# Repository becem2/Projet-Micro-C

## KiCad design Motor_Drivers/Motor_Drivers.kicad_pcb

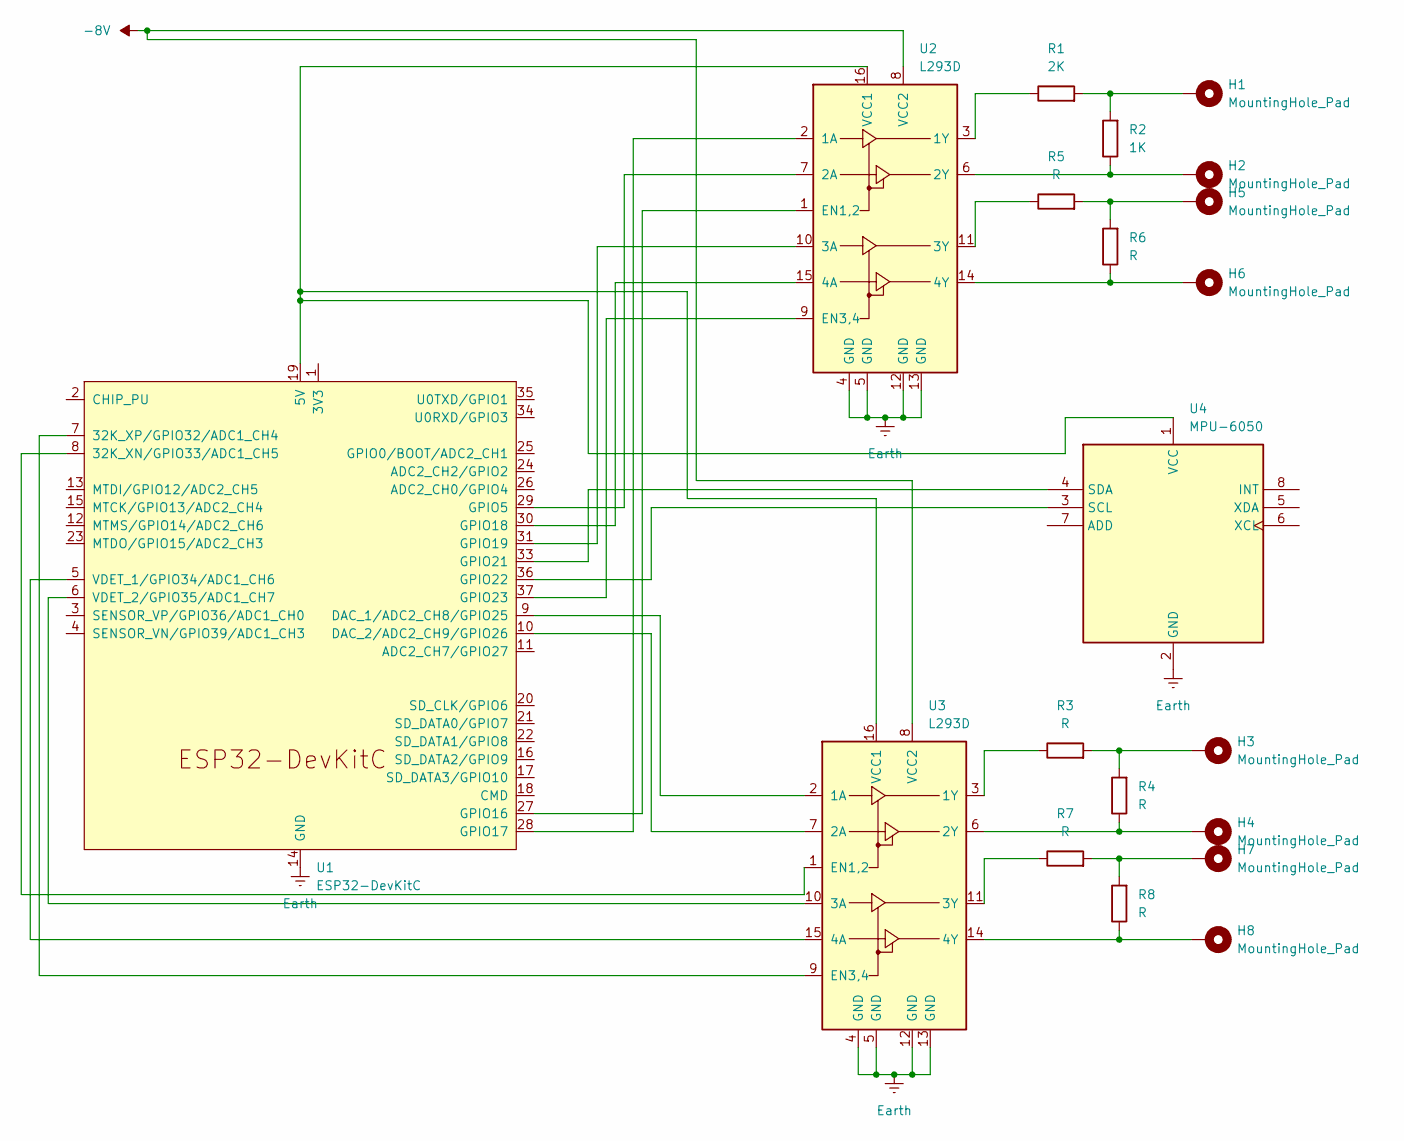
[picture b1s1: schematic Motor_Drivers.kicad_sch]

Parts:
H1, H2, H3, H4, H5, H6, H7, H8: MountingHole_Pad; TestPoint_Loop_D1.80mm_Drill1.0mm_Beaded
R1: 2K; R_Axial_DIN0204_L3.6mm_D1.6mm_P5.08mm_Horizontal
R2: 1K; R_Axial_DIN0204_L3.6mm_D1.6mm_P5.08mm_Horizontal
R3, R4, R5, R6, R7, R8: R; R_Axial_DIN0204_L3.6mm_D1.6mm_P5.08mm_Horizontal
U1: ESP32-DevKitC; ESP32_38pin
U2, U3: L293D; DIP-16_W7.62mm
U4: MPU-6050; module_mpu6050

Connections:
-8V: U2.8 (VCC2), U3.8 (VCC2)
Earth: U1.14 (GND), U1.32 (GND), U1.38 (GND), U2.4 (GND), U2.5 (GND), U2.12 (GND), U2.13 (GND), U3.4 (GND), U3.5 (GND), U3.12 (GND), U3.13 (GND), U4.2 (GND)
unnamed: H1.1, R1.2, R2.2
unnamed: H3.1, R3.2, R4.2
unnamed: H5.1, R5.2, R6.2
unnamed: H7.1, R7.2, R8.2
unnamed: U1.19 (5V), U2.16 (VCC1), U3.16 (VCC1), U4.1 (VCC)
unnamed: U1.8 (32K_XN/GPIO33/ADC1_CH5), U3.1 (EN1,2)
unnamed: U1.7 (32K_XP/GPIO32/ADC1_CH4), U3.9 (EN3,4)
unnamed: U1.9 (DAC_1/ADC2_CH8/GPIO25), U3.2 (1A)
unnamed: U1.10 (DAC_2/ADC2_CH9/GPIO26), U3.7 (2A)
unnamed: U1.29 (GPIO5), U2.7 (2A)
unnamed: U1.27 (GPIO16), U2.1 (EN1,2)
unnamed: U1.28 (GPIO17), U2.2 (1A)
unnamed: U1.30 (GPIO18), U2.15 (4A)
unnamed: U1.31 (GPIO19), U2.10 (3A)
unnamed: U1.33 (GPIO21), U4.4 (SDA)
unnamed: U1.36 (GPIO22), U4.3 (SCL)
unnamed: U1.37 (GPIO23), U2.9 (EN3,4)
unnamed: U1.5 (VDET_1/GPIO34/ADC1_CH6), U3.15 (4A)
unnamed: U1.6 (VDET_2/GPIO35/ADC1_CH7), U3.10 (3A)
unnamed: R1.1, U2.3 (1Y)
unnamed: H2.1, R2.1, U2.6 (2Y)
unnamed: R5.1, U2.11 (3Y)
unnamed: H6.1, R6.1, U2.14 (4Y)
unnamed: R3.1, U3.3 (1Y)
unnamed: H4.1, R4.1, U3.6 (2Y)
unnamed: R7.1, U3.11 (3Y)
unnamed: H8.1, R8.1, U3.14 (4Y)

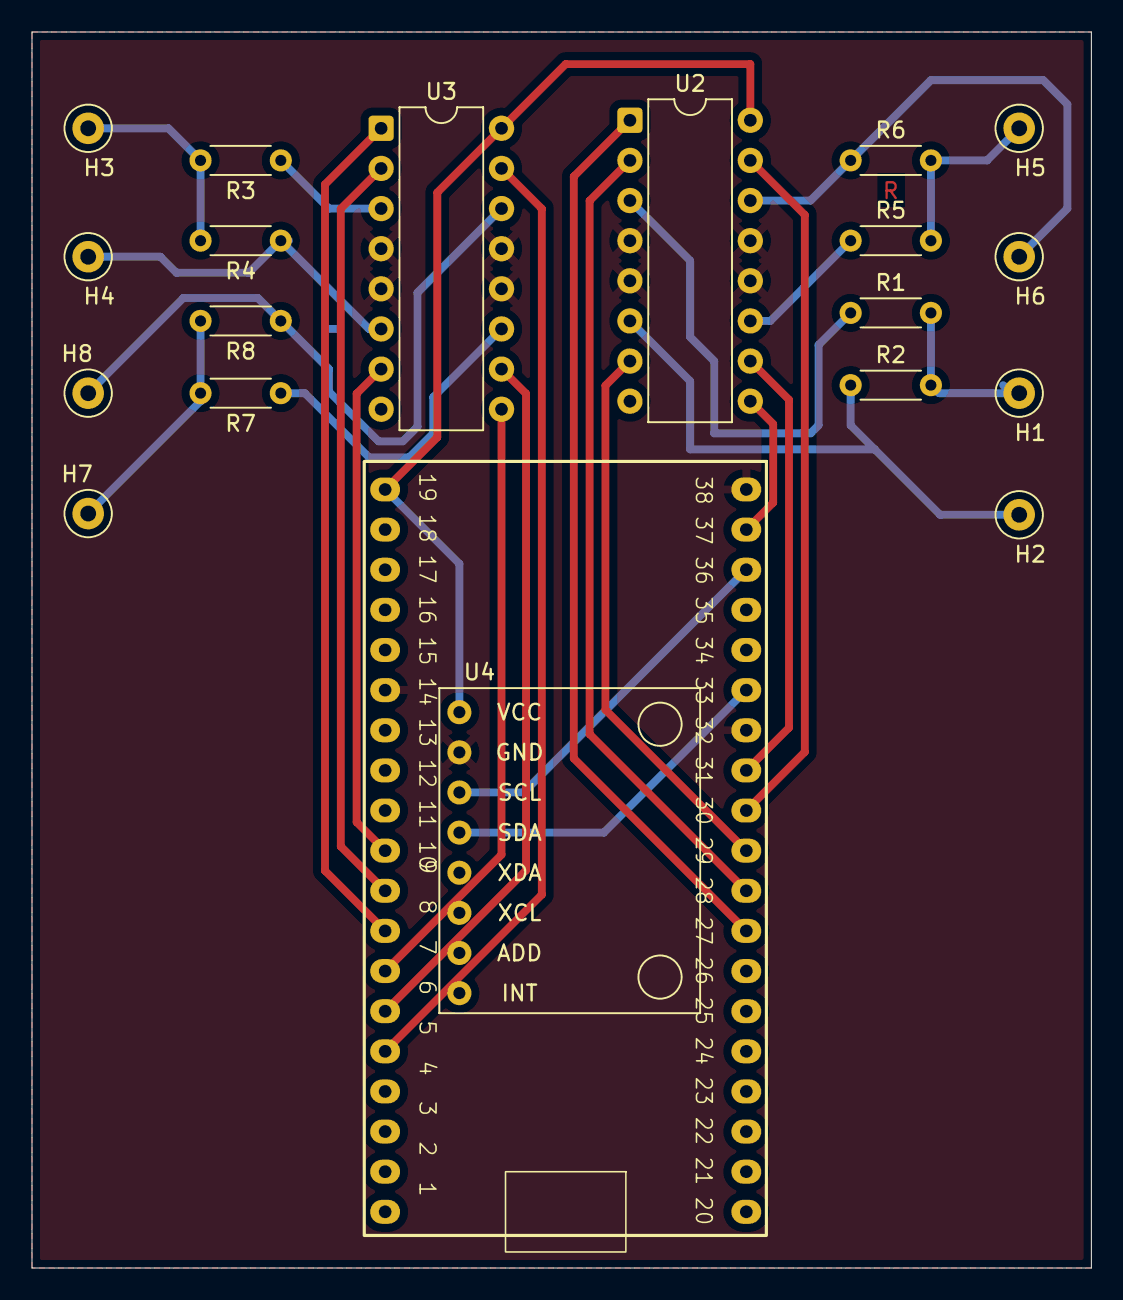
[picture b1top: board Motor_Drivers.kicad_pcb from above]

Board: 2 copper layers, 67.1 x 78.2 mm, 20 parts (0 on the bottom side), 29 nets.

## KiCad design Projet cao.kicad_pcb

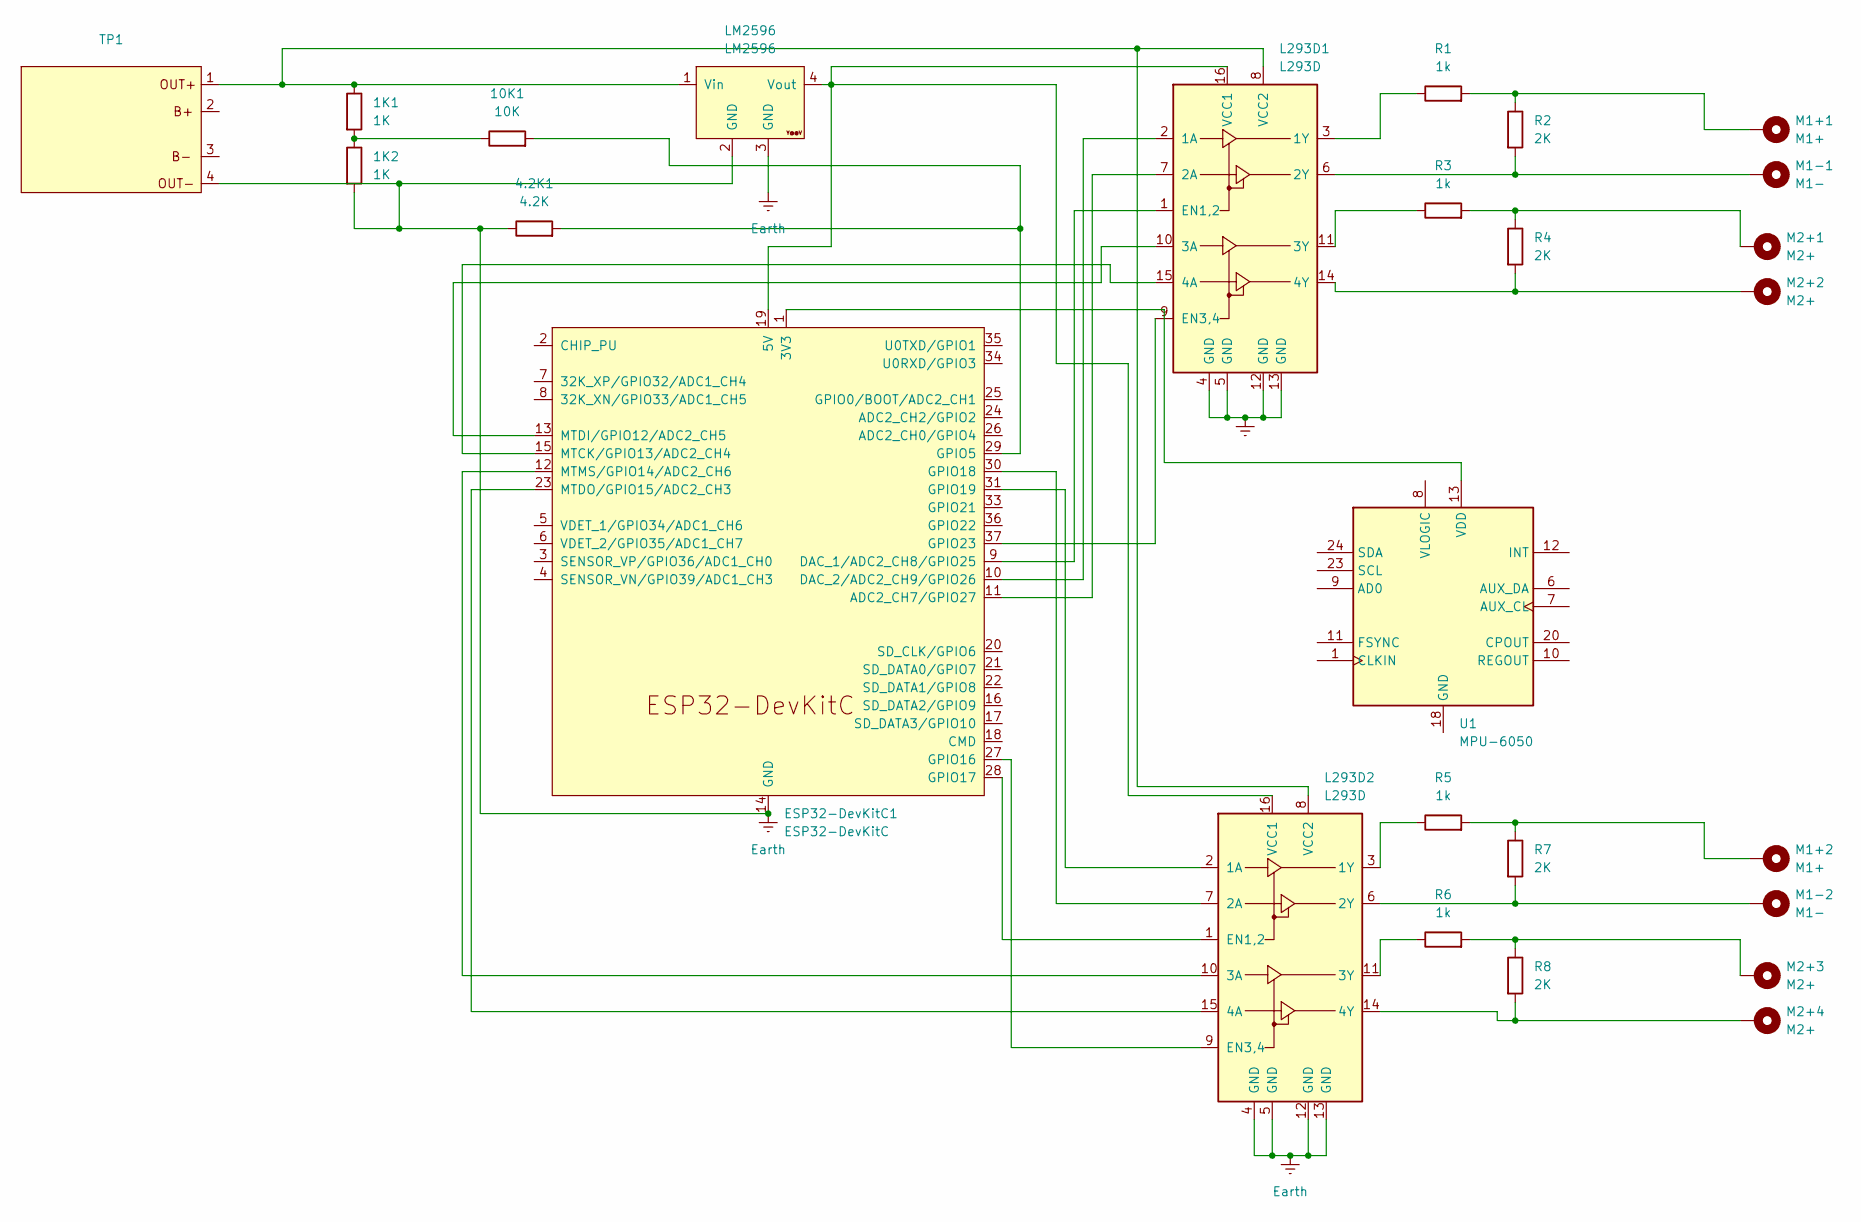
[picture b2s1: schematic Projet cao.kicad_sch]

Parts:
1K1, 1K2: 1K; R_Axial_DIN0204_L3.6mm_D1.6mm_P5.08mm_Horizontal
4.2K1: 4.2K; R_Axial_DIN0204_L3.6mm_D1.6mm_P5.08mm_Horizontal
10K1: 10K; R_Axial_DIN0204_L3.6mm_D1.6mm_P5.08mm_Horizontal
ESP32-DevKitC1: ESP32-DevKitC; ESP32_38pin
L293D1, L293D2: L293D; DIP-16_W7.62mm
LM2596: LM2596; YAAJ_DCDC_StepDown_LM2596
M1+1, M1+2: M1+; MountingHole_2.2mm_M2_ISO7380_Pad
M1-1, M1-2: M1-; MountingHole_2.2mm_M2_ISO7380_Pad
M2+1, M2+2, M2+3, M2+4: M2+; MountingHole_2.2mm_M2_ISO7380_Pad
R1, R3, R5, R6: 1k; R_Axial_DIN0204_L3.6mm_D1.6mm_P5.08mm_Horizontal
R2, R4, R7, R8: 2K; R_Axial_DIN0204_L3.6mm_D1.6mm_P5.08mm_Horizontal
TP1: TP4056-18650
U1: MPU-6050; module_mpu6050

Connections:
Earth: 1K2.2, 4.2K1.1, ESP32-DevKitC1.14 (GND), ESP32-DevKitC1.32 (GND), ESP32-DevKitC1.38 (GND), L293D1.4 (GND), L293D1.5 (GND), L293D1.12 (GND), L293D1.13 (GND), L293D2.4 (GND), L293D2.5 (GND), L293D2.12 (GND), L293D2.13 (GND), LM2596.2 (GND), LM2596.3 (GND), TP1.4
unnamed: 1K1.2, 1K2.1, 10K1.1
unnamed: ESP32-DevKitC1.1 (3V3), U1.13 (VDD)
unnamed: ESP32-DevKitC1.19 (5V), L293D1.16 (VCC1), L293D2.16 (VCC1), LM2596.4 (Vout)
unnamed: ESP32-DevKitC1.11 (ADC2_CH7/GPIO27), L293D1.7 (2A)
unnamed: ESP32-DevKitC1.9 (DAC_1/ADC2_CH8/GPIO25), L293D1.1 (EN1,2)
unnamed: ESP32-DevKitC1.10 (DAC_2/ADC2_CH9/GPIO26), L293D1.2 (1A)
unnamed: 4.2K1.2, 10K1.2, ESP32-DevKitC1.29 (GPIO5)
unnamed: ESP32-DevKitC1.27 (GPIO16), L293D2.9 (EN3,4)
unnamed: ESP32-DevKitC1.28 (GPIO17), L293D2.1 (EN1,2)
unnamed: ESP32-DevKitC1.30 (GPIO18), L293D2.7 (2A)
unnamed: ESP32-DevKitC1.31 (GPIO19), L293D2.2 (1A)
unnamed: ESP32-DevKitC1.37 (GPIO23), L293D1.9 (EN3,4)
unnamed: ESP32-DevKitC1.15 (MTCK/GPIO13/ADC2_CH4), L293D1.15 (4A)
unnamed: ESP32-DevKitC1.13 (MTDI/GPIO12/ADC2_CH5), L293D1.10 (3A)
unnamed: ESP32-DevKitC1.23 (MTDO/GPIO15/ADC2_CH3), L293D2.15 (4A)
unnamed: ESP32-DevKitC1.12 (MTMS/GPIO14/ADC2_CH6), L293D2.10 (3A)
unnamed: L293D1.3 (1Y), R1.1
unnamed: L293D1.6 (2Y), M1-1.1, R2.2
unnamed: L293D1.11 (3Y), R3.1
unnamed: L293D1.14 (4Y), M2+2.1, R4.2
unnamed: 1K1.1, L293D1.8 (VCC2), L293D2.8 (VCC2), LM2596.1 (Vin), TP1.1
unnamed: L293D2.3 (1Y), R5.1
unnamed: L293D2.6 (2Y), M1-2.1, R7.2
unnamed: L293D2.11 (3Y), R6.1
unnamed: L293D2.14 (4Y), M2+4.1, R8.2
unnamed: M1+1.1, R1.2, R2.1
unnamed: M1+2.1, R5.2, R7.1
unnamed: M2+1.1, R3.2, R4.1
unnamed: M2+3.1, R6.2, R8.1

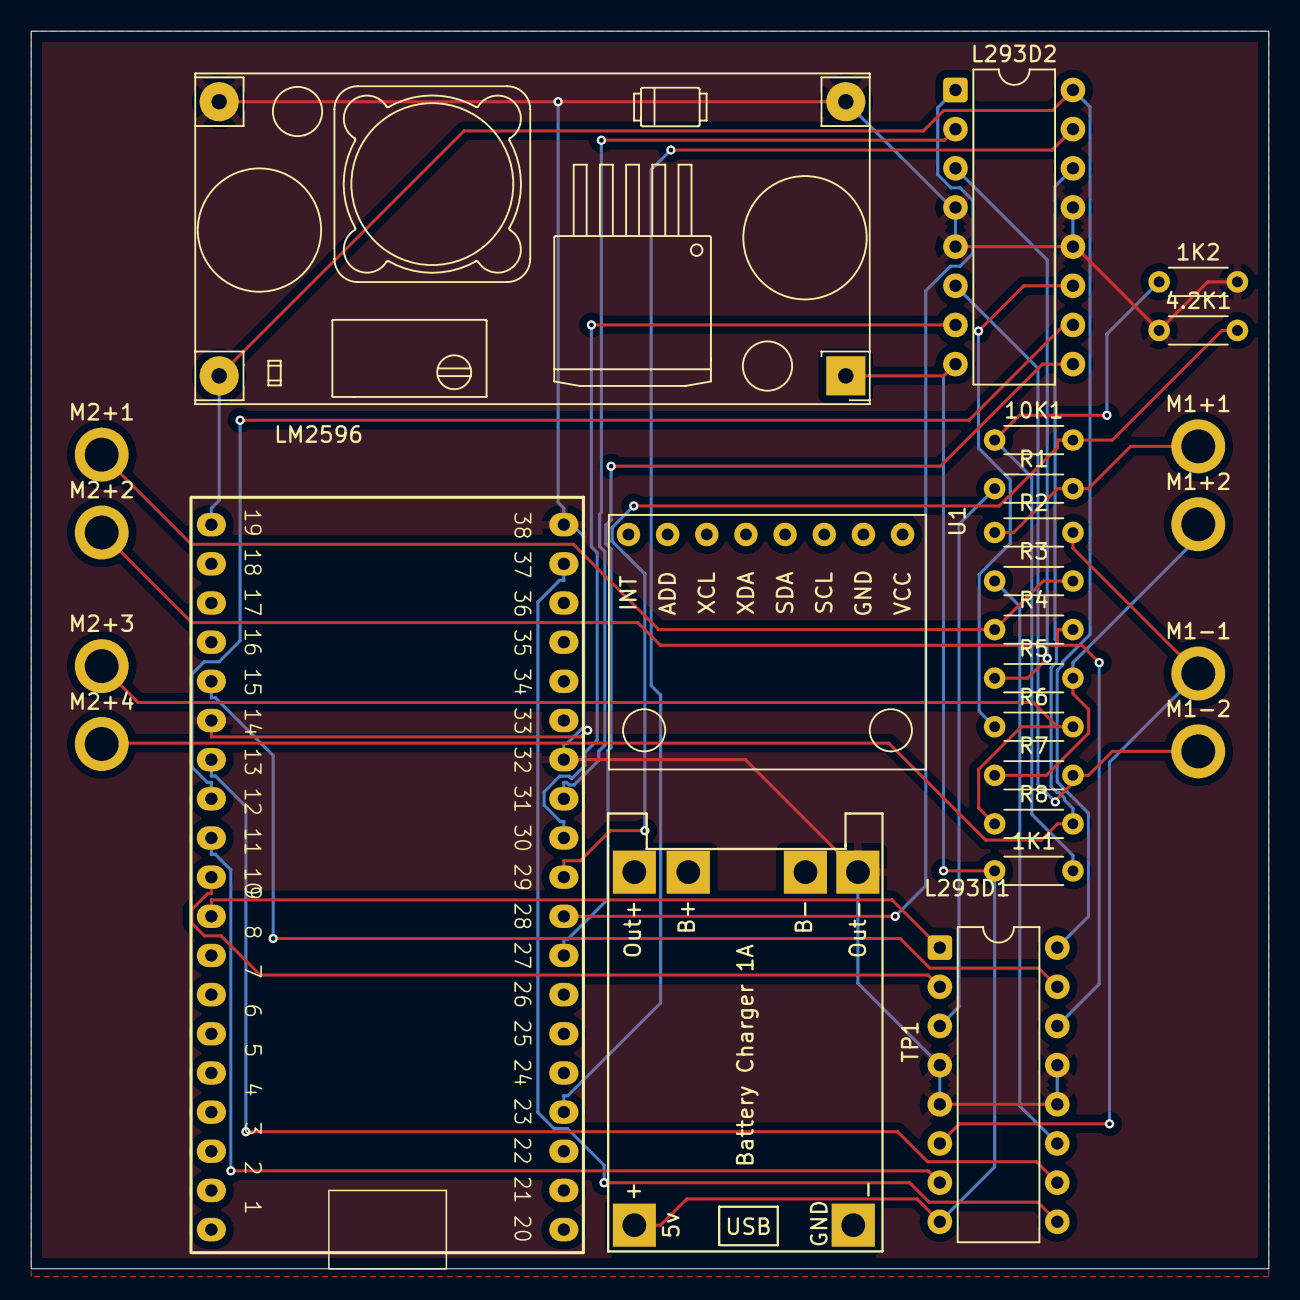
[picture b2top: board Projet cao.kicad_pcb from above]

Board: 2 copper layers, 80.3 x 80.3 mm, 26 parts (0 on the bottom side), 29 nets.

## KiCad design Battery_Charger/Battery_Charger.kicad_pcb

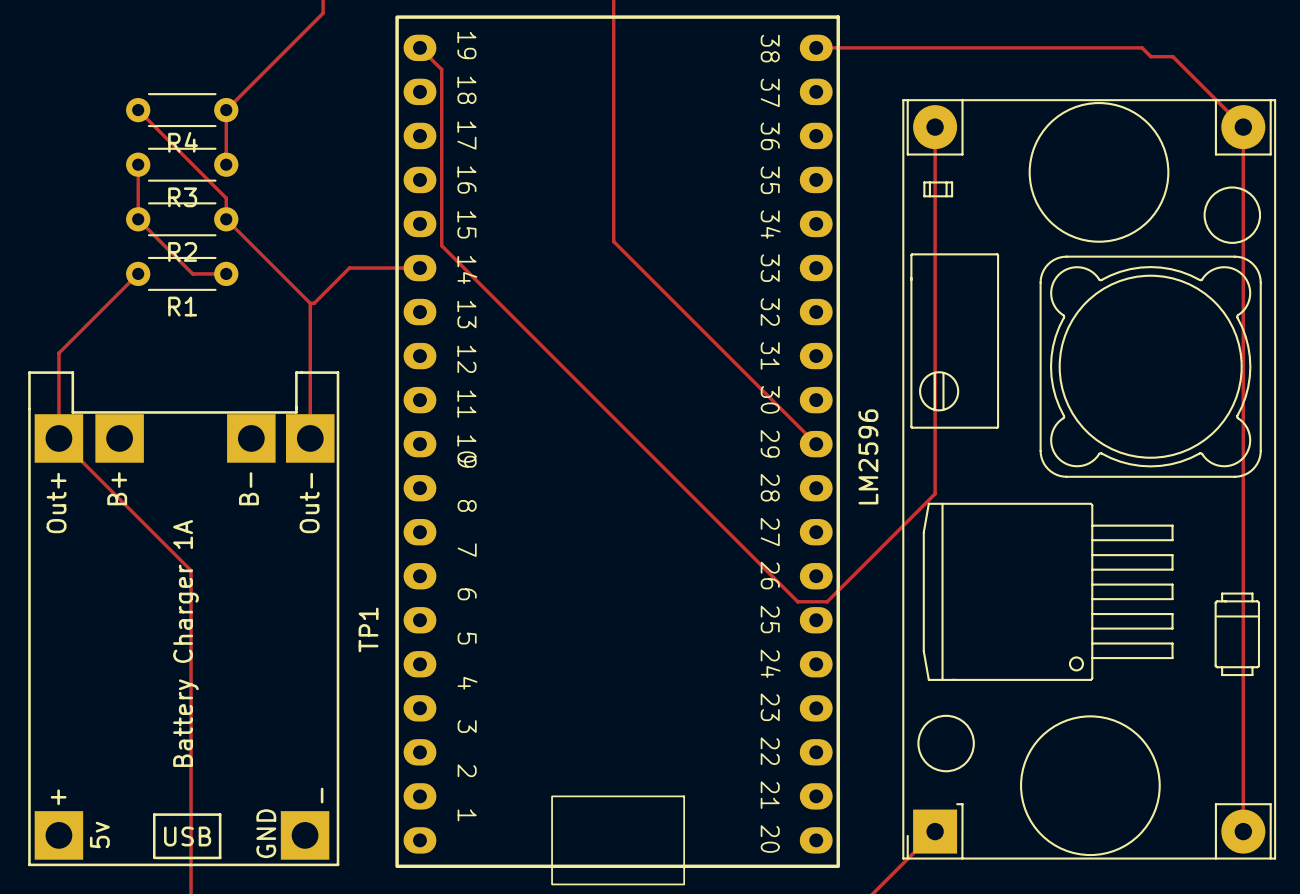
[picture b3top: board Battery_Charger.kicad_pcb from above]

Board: 2 copper layers, 7 parts (0 on the bottom side), 5 nets.

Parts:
LM2596: LM2596; YAAJ_DCDC_StepDown_LM2596
R1, R2: 1K; R_Axial_DIN0204_L3.6mm_D1.6mm_P5.08mm_Horizontal
R3: 10K; R_Axial_DIN0204_L3.6mm_D1.6mm_P5.08mm_Horizontal
R4: 4K; R_Axial_DIN0204_L3.6mm_D1.6mm_P5.08mm_Horizontal
TP1: TP4056-18650
U1: ESP32-DevKitC; ESP32_38pin

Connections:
unnamed: LM2596.2 (GND), LM2596.3 (GND), R2.1, R4.2, TP1.4, U1.14 (GND), U1.32 (GND), U1.38 (GND)
unnamed: LM2596.1 (Vin), R1.2, TP1.3
unnamed: LM2596.4 (Vout), U1.19 (5V)
unnamed: R1.1, R2.2, R3.2
unnamed: R3.1, R4.1, U1.29 (GPIO5)

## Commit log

2025-04-11 Projet
2025-07-09 Drone
